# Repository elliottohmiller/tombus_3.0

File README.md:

# tombus_3.0
A barebones noisemaker with a focus on intuitive controls.

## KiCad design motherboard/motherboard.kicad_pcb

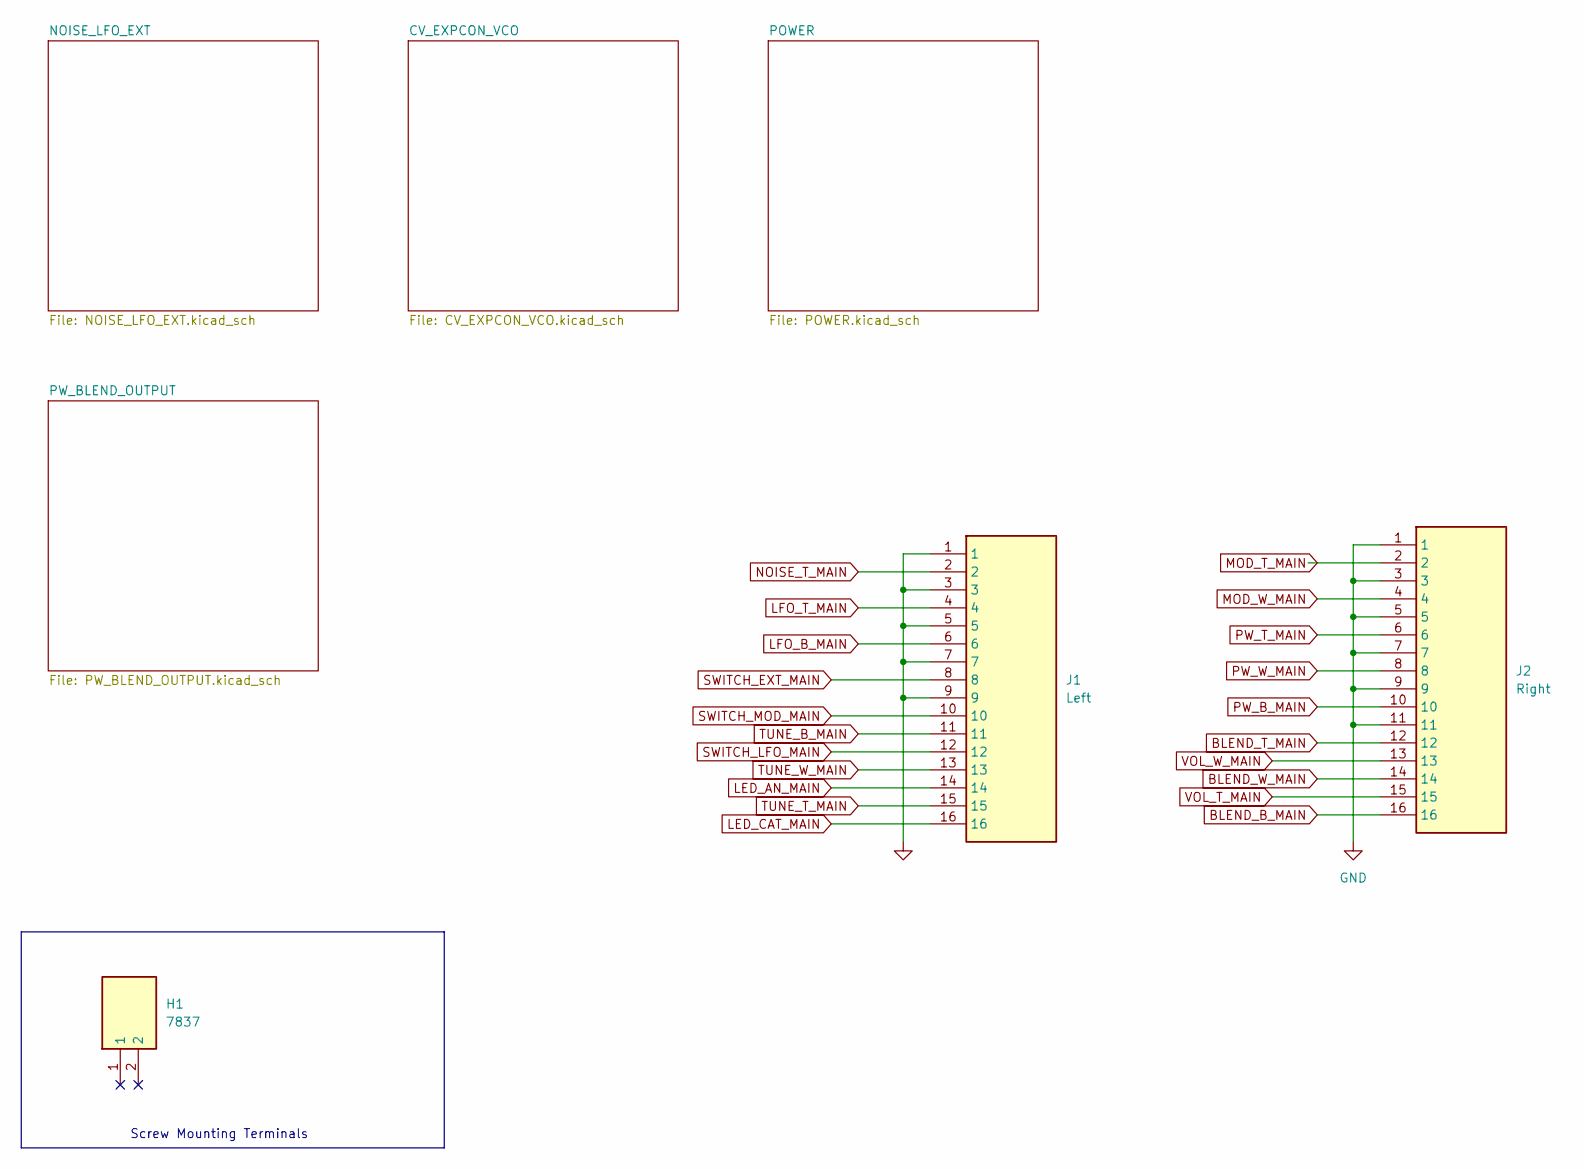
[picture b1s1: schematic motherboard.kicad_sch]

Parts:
H1: 7837; Mouser Part Number 534-7837
J1: Left; HLW16R2C7LF; Mouser Part Number 649-HLW16R-2C7LF
J2: Right; HLW16R2C7LF; Mouser Part Number 649-HLW16R-2C7LF

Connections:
BLEND_B_MAIN: J2.16; also elsewhere on the board
BLEND_T_MAIN: J2.12; also elsewhere on the board
BLEND_W_MAIN: J2.14; also elsewhere on the board
GND: J1.1, J1.3, J1.5, J1.7, J1.9, J2.1, J2.3, J2.5, J2.7, J2.9, J2.11; also elsewhere on the board
LED_AN_MAIN: J1.14; also elsewhere on the board
LED_CAT_MAIN: J1.16; also elsewhere on the board
LFO_B_MAIN: J1.6; also elsewhere on the board
LFO_T_MAIN: J1.4; also elsewhere on the board
MOD_T_MAIN: J2.2; also elsewhere on the board
MOD_W_MAIN: J2.4; also elsewhere on the board
NOISE_T_MAIN: J1.2; also elsewhere on the board
PW_B_MAIN: J2.10; also elsewhere on the board
PW_T_MAIN: J2.6; also elsewhere on the board
PW_W_MAIN: J2.8; also elsewhere on the board
SWITCH_EXT_MAIN: J1.8; also elsewhere on the board
SWITCH_LFO_MAIN: J1.12; also elsewhere on the board
SWITCH_MOD_MAIN: J1.10; also elsewhere on the board
TUNE_B_MAIN: J1.11; also elsewhere on the board
TUNE_T_MAIN: J1.15; also elsewhere on the board
TUNE_W_MAIN: J1.13; also elsewhere on the board
VOL_T_MAIN: J2.15; also elsewhere on the board
VOL_W_MAIN: J2.13; also elsewhere on the board

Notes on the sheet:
Screw Mounting Terminals

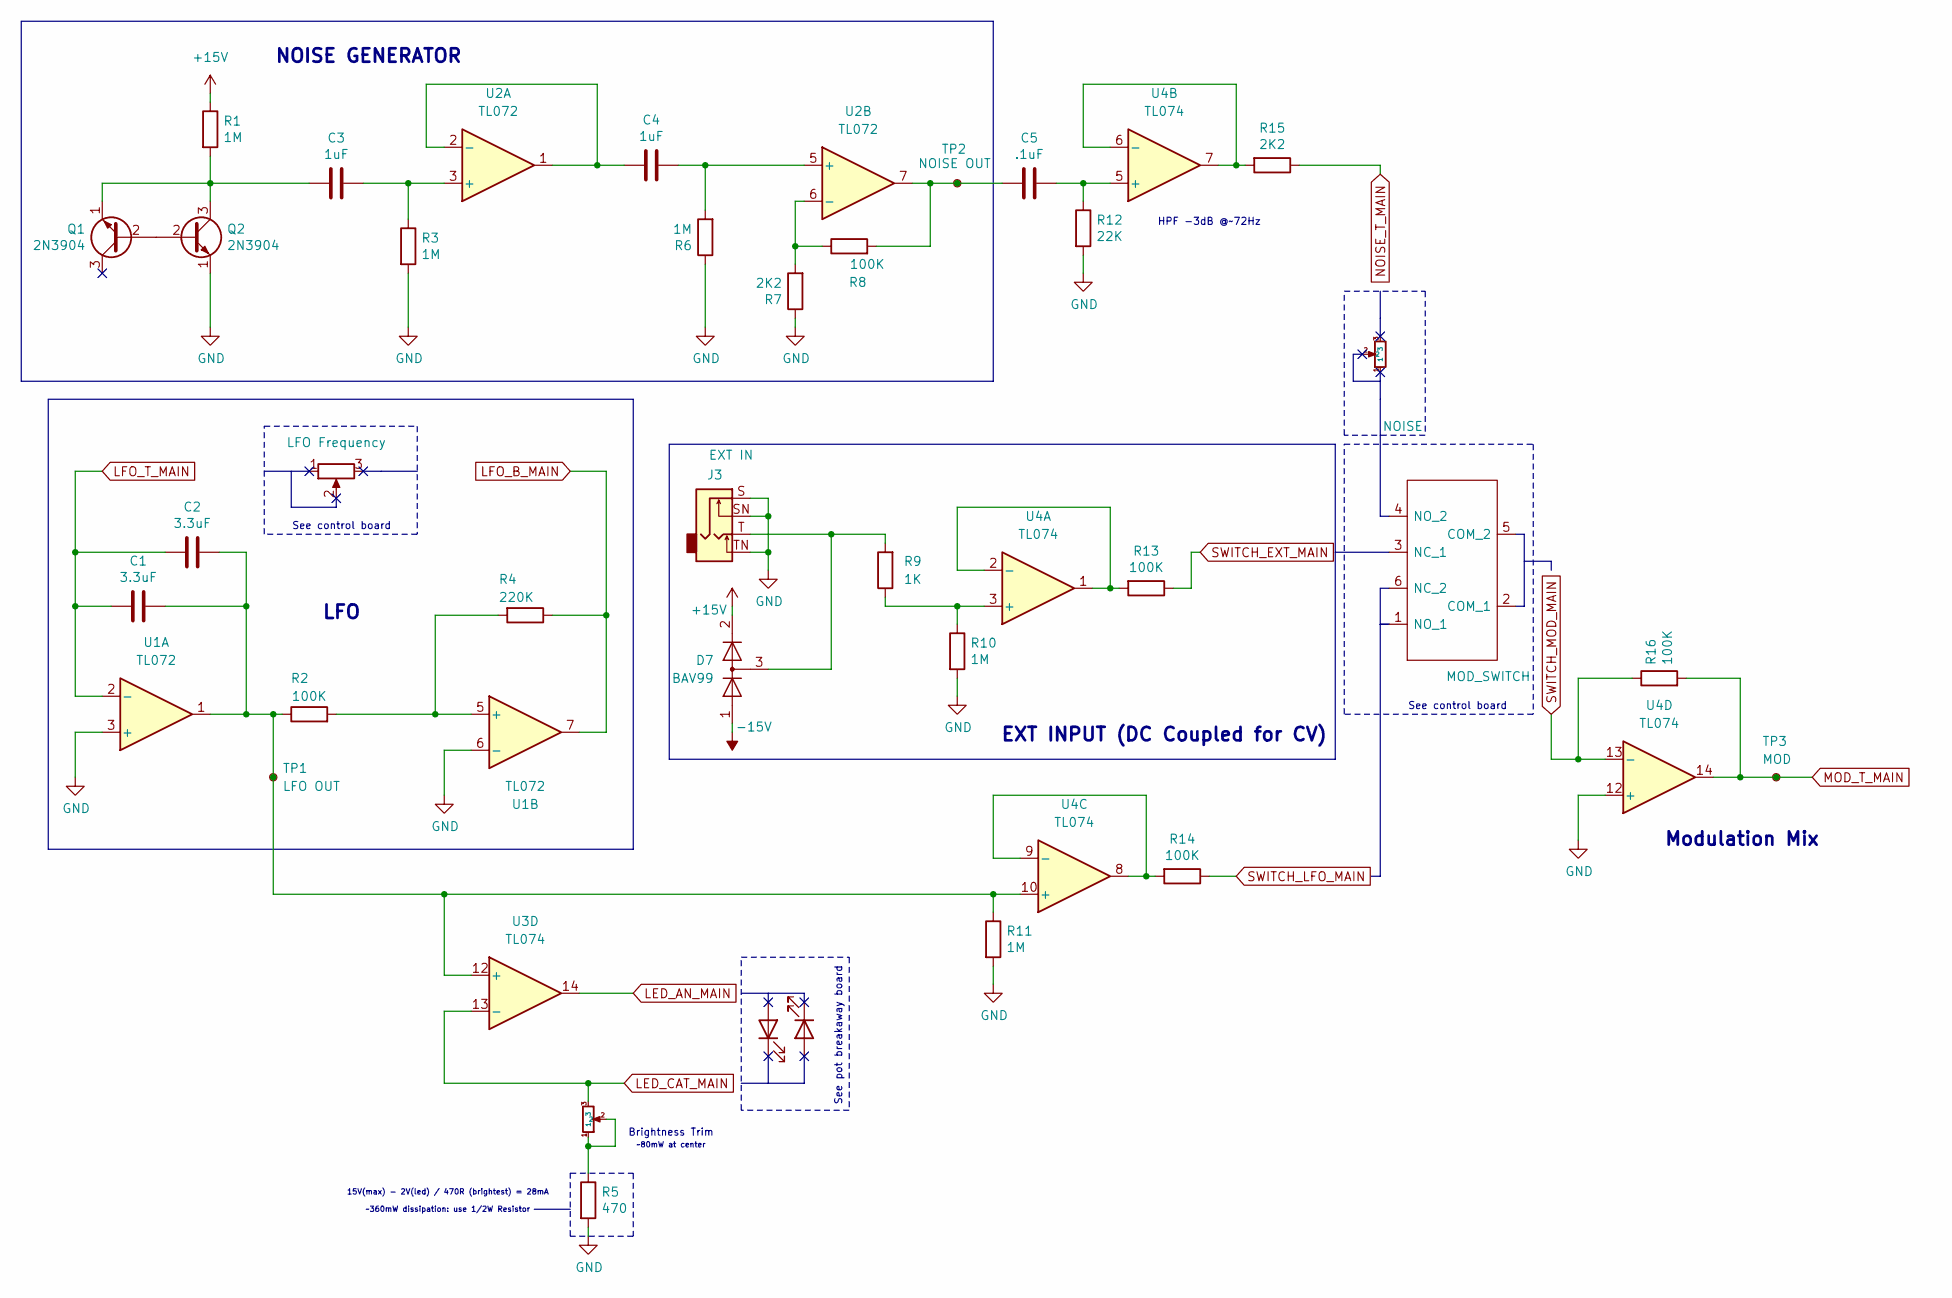
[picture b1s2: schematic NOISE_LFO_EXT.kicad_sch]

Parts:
C1, C2: 3.3uF; C_Rect_L18.0mm_W7.0mm_P15.00mm_FKS3_FKP3
C3, C4: 1uF; C_Rect_L7.2mm_W4.5mm_P5.00mm_FKS2_FKP2_MKS2_MKP2
C5: .1uF; C_Rect_L7.0mm_W2.0mm_P5.00mm
D1, D2: LFO F
D7: BAV99; SOT-23
J3: EXT IN; Jack_6.35mm_Neutrik_NMJ4HFD2_Horizontal
Q1, Q2: 2N3904; TO-92_HandSolder
R1, R3, R6, R10, R11: 1M; RESC2012X60N
R2, R8, R13, R14, R16: 100K; RESC2012X60N
R4: 220K; RESC2012X60N
R5: 470; R_Axial_DIN0207_L6.3mm_D2.5mm_P10.16mm_Horizontal
R7, R15: 2K2; RESC2012X60N
R9: 1K; RESC2012X60N
R12: 22K; RESC2012X60N
RV1: LFO Frequency
S1: MOD_SWITCH; 7211SYCQE; Mouser Part Number 611-7211-002
TP1: LFO OUT; TestPoint_Pad_D1.5mm
TP2: NOISE OUT; TestPoint_Pad_D1.5mm
TP3: MOD; TestPoint_Pad_D1.5mm
U1, U2: TL072; DIP-8_W7.62mm_Socket
U3, U4: TL074; DIP-14_W7.62mm_Socket
VR1: LED BRIGHTNESS; Potentiometer_Vishay_T73XX_Horizontal; Mouser Part Number 72-T70YP-10K
VR2: NOISE; T73YP103KT20; Mouser Part Number 72-T70YP-10K

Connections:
+15V: D7.2 (A), R1.1; also elsewhere on the board
-15V: D7.1 (K); also elsewhere on the board
GND: J3.S, J3.SN, J3.TN, Q2.1 (E), R3.2, R5.2, R6.1, R7.1, R10.2, R11.2, R12.2, U1.3 (+), U1.6 (-), U4.12 (+); also elsewhere on the board
LED_AN_MAIN: U3.14; also elsewhere on the board
LED_CAT_MAIN: U3.13 (-), VR1.3; also elsewhere on the board
LFO_B_MAIN: R4.1, U1.7; also elsewhere on the board
LFO_T_MAIN: C1.2, C2.2, U1.2 (-); also elsewhere on the board
MOD_T_MAIN: R16.2, TP3.1, U4.14; also elsewhere on the board
NOISE_T_MAIN: R15.1; also elsewhere on the board
unnamed: C5.2, R8.2, TP2.1, U2.7
unnamed: D7.3 (K), J3.T, R9.2
unnamed: Q1.2 (B), Q2.2 (B)
unnamed: C3.2, Q1.1 (E), Q2.3 (C), R1.2
unnamed: R5.1, VR1.1, VR1.2
unnamed: R2.2, R4.2, U1.5 (+)
unnamed: C3.1, R3.1, U2.3 (+)
unnamed: C4.2, U2.1, U2.2 (-)
unnamed: C4.1, R6.2, U2.5 (+)
unnamed: R7.2, R8.1, U2.6 (-)
unnamed: C1.1, C2.1, R2.1, R11.1, TP1.1, U1.1, U3.12 (+), U4.10 (+)
unnamed: R9.1, R10.1, U4.3 (+)
unnamed: R13.2, U4.1, U4.2 (-)
unnamed: C5.1, R12.1, U4.5 (+)
unnamed: R15.2, U4.6 (-), U4.7
unnamed: R14.2, U4.8, U4.9 (-)
SWITCH_EXT_MAIN: R13.1; also elsewhere on the board
SWITCH_LFO_MAIN: R14.1; also elsewhere on the board
SWITCH_MOD_MAIN: R16.1, U4.13 (-); also elsewhere on the board

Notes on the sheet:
Brightness Trim
NOISE GENERATOR
LFO
15V(max) - 2V(led) / 470R (brightest) = 28mA ~360mW dissipation: use 1/2W Resistor
See control board
See pot breakaway board
~80mW at center
HPF -3dB @~72Hz
EXT INPUT (DC Coupled for CV)
Modulation Mix

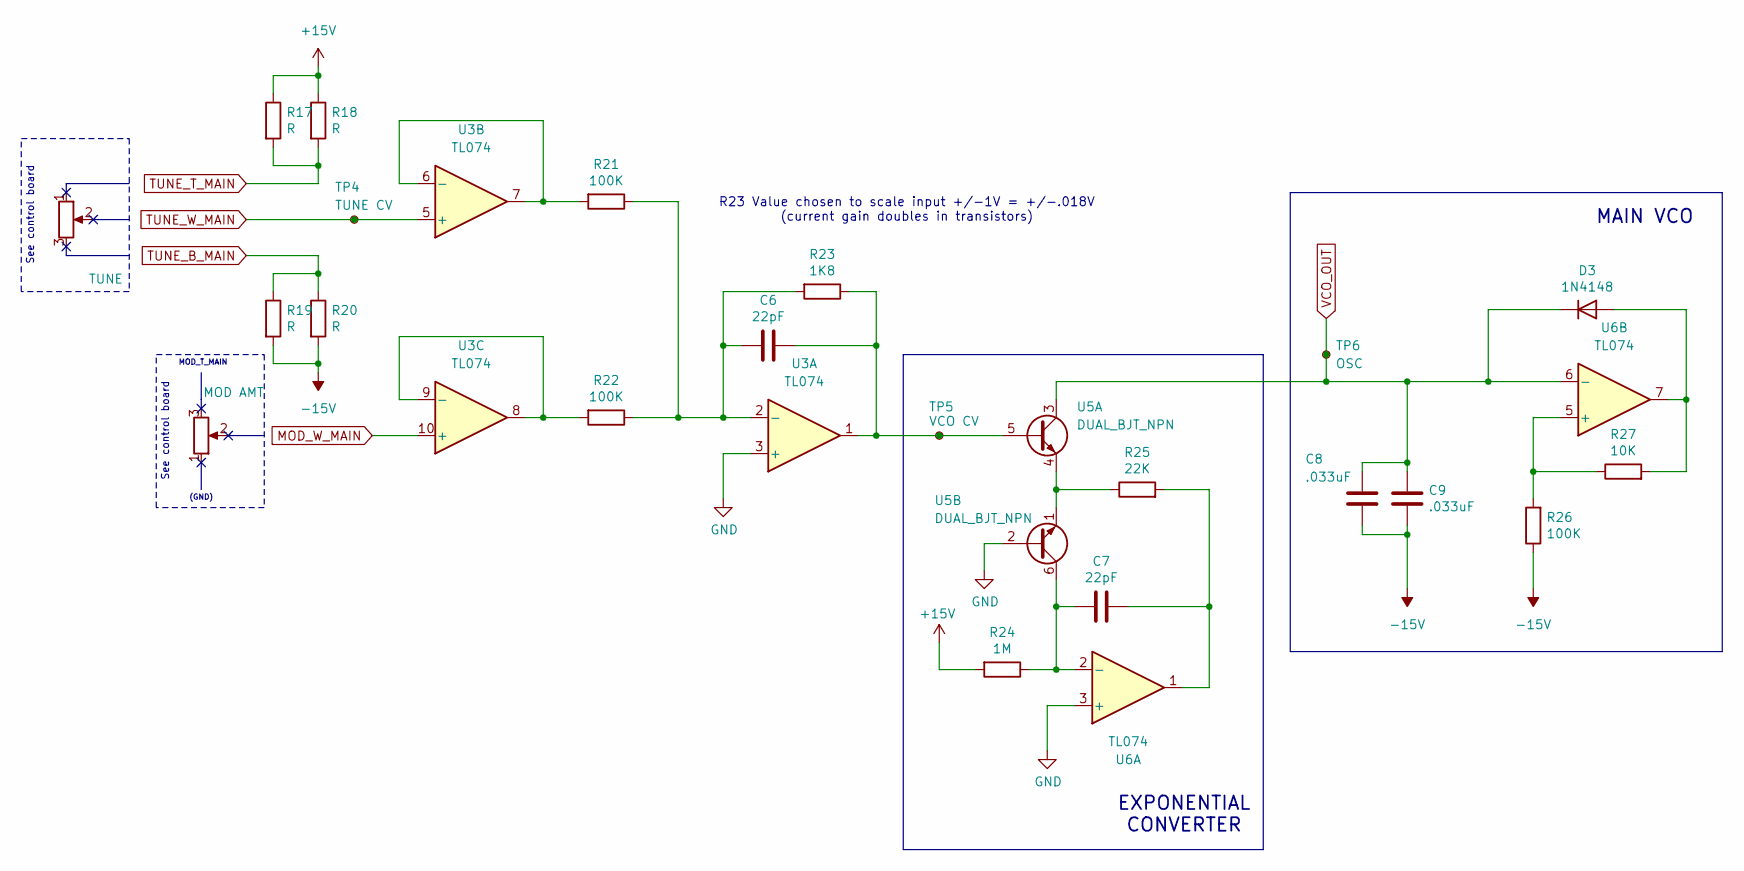
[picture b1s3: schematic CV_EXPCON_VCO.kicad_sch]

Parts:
C6, C7: 22pF; C0805
C8, C9: .033uF; C_Rect_L7.2mm_W8.5mm_P5.00mm_FKP2_FKP2_MKS2_MKP2
D3: 1N4148; D_DO-35_SOD27_P7.62mm_Horizontal
R17, R18, R19, R20: R; RESC2012X60N
R21, R22, R26: 100K; RESC2012X60N
R23: 1K8; RESC2012X60N
R24: 1M; RESC2012X60N
R25: 22K; RESC2012X60N
R27: 10K; RESC2012X60N
RV2: TUNE
RV3: MOD AMT
TP4: TUNE CV; TestPoint_Pad_D1.5mm
TP5: VCO CV; TestPoint_Pad_D1.5mm
TP6: OSC; TestPoint_Pad_D1.5mm
U3, U6: TL074; DIP-14_W7.62mm_Socket
U5: DUAL_BJT_NPN; SOT-363_SC-70-6

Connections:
+15V: R17.1, R18.1, R24.2; also elsewhere on the board
-15V: C8.1, C9.1, R19.2, R20.2, R26.1; also elsewhere on the board
GND: U3.3 (+), U5.2 (B1), U6.3 (+); also elsewhere on the board
MOD_W_MAIN: U3.10 (+); also elsewhere on the board
unnamed: C7.1, R25.2, U6.1
unnamed: D3.2 (A), R27.2, U6.7
unnamed: C6.2, R21.1, R22.1, R23.2, U3.2 (-)
unnamed: R21.2, U3.6 (-), U3.7
unnamed: R22.2, U3.8, U3.9 (-)
unnamed: C6.1, R23.1, TP5.1, U3.1, U5.5 (B2)
unnamed: R25.1, U5.1 (E2), U5.4 (E1)
unnamed: C7.2, R24.1, U5.6 (C2), U6.2 (-)
unnamed: R26.2, R27.1, U6.5 (+)
TUNE_B_MAIN: R19.1, R20.1; also elsewhere on the board
TUNE_T_MAIN: R17.2, R18.2; also elsewhere on the board
TUNE_W_MAIN: TP4.1, U3.5 (+); also elsewhere on the board
VCO_OUT: C8.2, C9.2, D3.1 (K), TP6.1, U5.3 (C1), U6.6 (-); also elsewhere on the board

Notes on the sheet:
See control board
MOD_T_MAIN
R23 Value chosen to scale input +/-1V = +/-.018V (current gain doubles in transistors)
MAIN VCO
EXPONENTIAL CONVERTER
(GND)

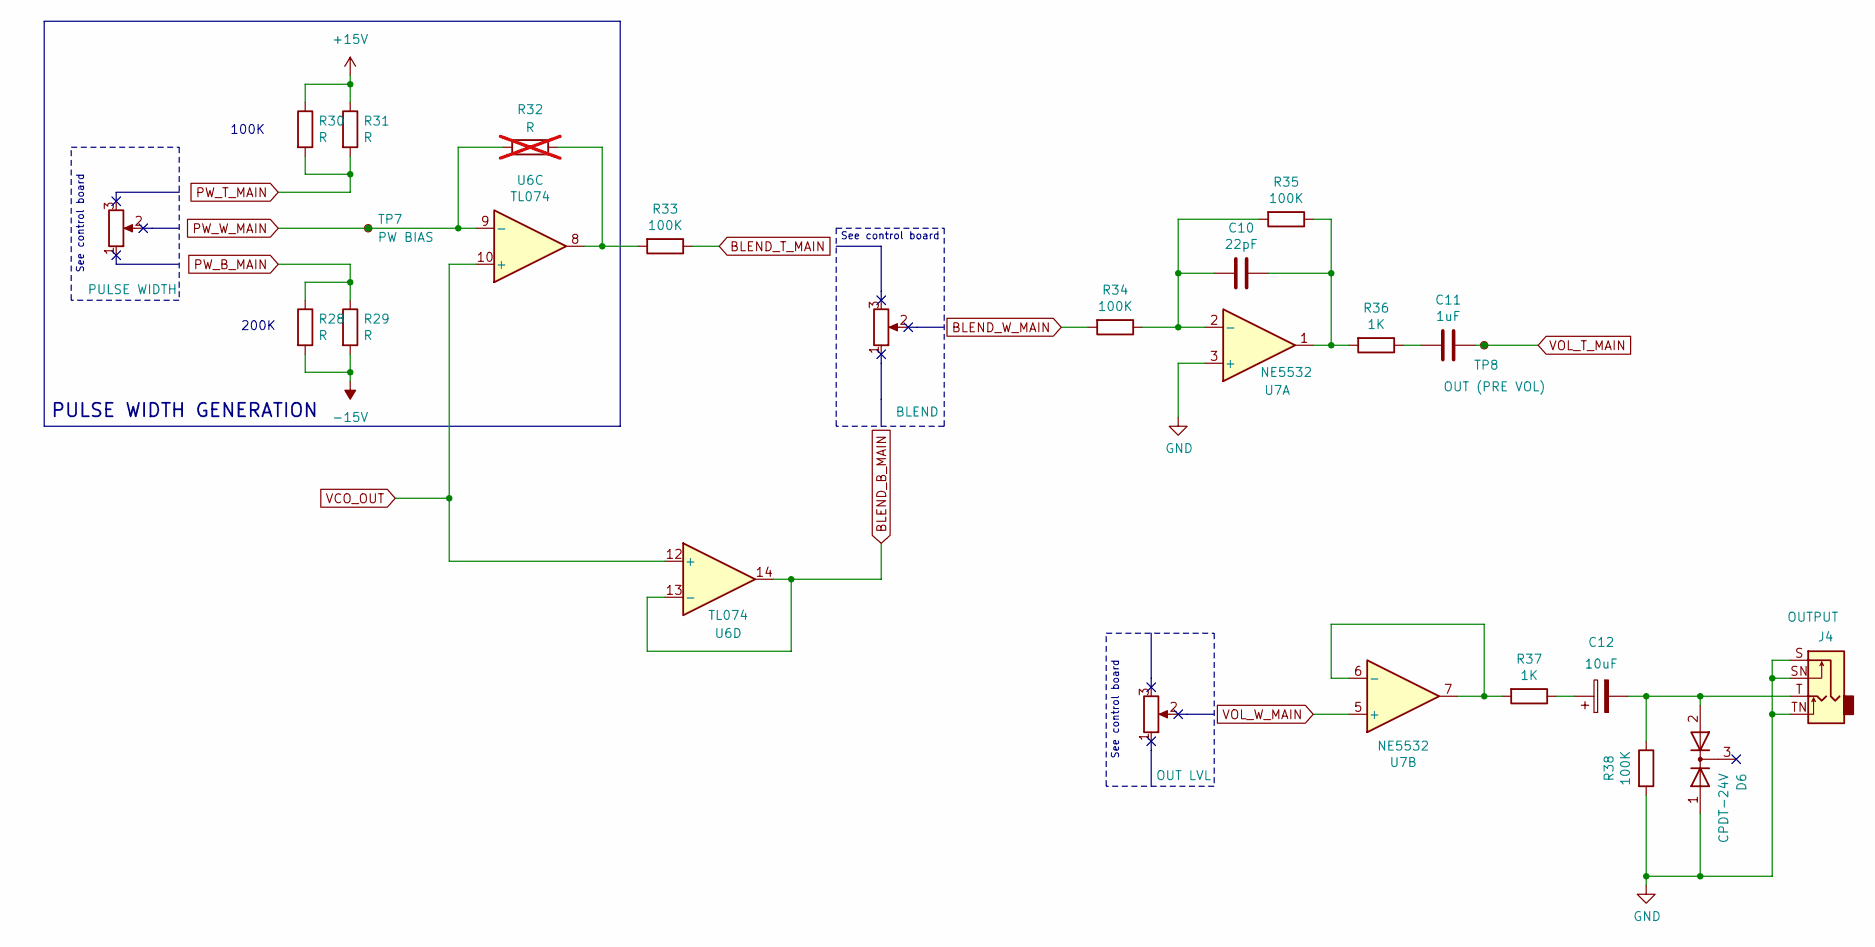
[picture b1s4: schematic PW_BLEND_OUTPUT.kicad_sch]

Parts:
C10: 22pF; C0805
C11: 1uF; C_Rect_L7.2mm_W4.5mm_P5.00mm_FKS2_FKP2_MKS2_MKP2
C12: 10uF; CP_Radial_D5.0mm_P2.00mm
D6: CPDT-24V; SOT-23
J4: OUTPUT; Jack_6.35mm_Neutrik_NMJ4HFD2_Horizontal
R28, R29, R30, R31: R; RESC2012X60N
R32: R; RESC2012X60N; not fitted
R33, R34, R35, R38: 100K; RESC2012X60N
R36, R37: 1K; RESC2012X60N
RV4: PULSE WIDTH
RV5: BLEND
RV6: OUT LVL
TP7: PW BIAS; TestPoint_Pad_D1.5mm
TP8: OUT (PRE VOL); TestPoint_Pad_D1.5mm
U6: TL074; DIP-14_W7.62mm_Socket
U7: NE5532; DIP-8_W7.62mm_Socket

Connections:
+15V: R30.1, R31.1; also elsewhere on the board
-15V: R28.2, R29.2; also elsewhere on the board
BLEND_B_MAIN: U6.13 (-), U6.14; also elsewhere on the board
BLEND_T_MAIN: R33.1; also elsewhere on the board
BLEND_W_MAIN: R34.2; also elsewhere on the board
GND: D6.1 (A), J4.S, J4.SN, J4.TN, R38.2, U7.3 (+); also elsewhere on the board
unnamed: C10.1, R35.1, R36.2, U7.1
unnamed: C11.2, R36.1
unnamed: C12.1, R37.1
unnamed: C12.2, D6.2 (A), J4.T, R38.1
unnamed: R32.2, R33.2, U6.8
unnamed: C10.2, R34.1, R35.2, U7.2 (-)
unnamed: R37.2, U7.6 (-), U7.7
PW_B_MAIN: R28.1, R29.1; also elsewhere on the board
PW_T_MAIN: R30.2, R31.2; also elsewhere on the board
PW_W_MAIN: R32.1, TP7.1, U6.9 (-); also elsewhere on the board
VCO_OUT: U6.10 (+), U6.12 (+); also elsewhere on the board
VOL_T_MAIN: C11.1, TP8.1; also elsewhere on the board
VOL_W_MAIN: U7.5 (+); also elsewhere on the board

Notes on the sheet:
See control board
200K
100K
PULSE WIDTH GENERATION

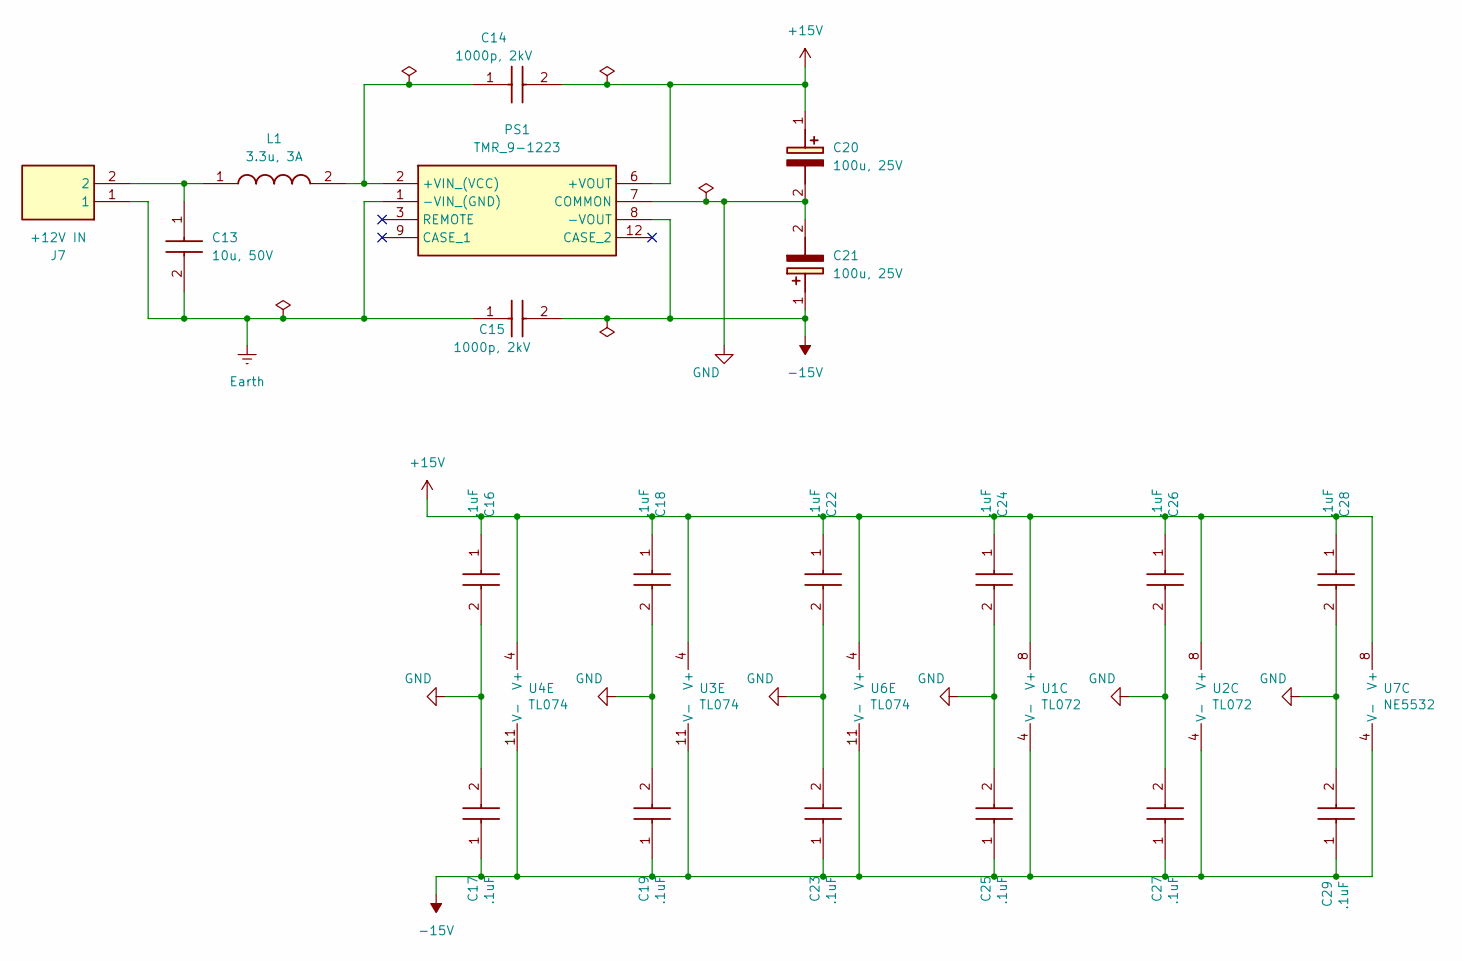
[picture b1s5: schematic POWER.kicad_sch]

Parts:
C13: 10u, 50V; C1210; Mouser Part Number 80-C1210C106M5R
C14, C15: 1000p, 2kV; C1206; Mouser Part Number 80-C1206C102JGR
C16, C17, C18, C19, C22, C23, C24, C25, C26, C27, C28, C29: .1uF; C0805; Mouser Part Number 80-C0805C104K1R
C20, C21: 100u, 25V; CAPPRD250W55D630H1350; Mouser Part Number 581-RES0611101M025B
J7: +12V IN; SHDR2W66P0X254_1X2_508X572X1041P; Mouser Part Number 571-6404562
L1: 3.3u, 3A; INDPM4740X210N; Mouser Part Number 495-TCK-108
PS1: TMR_9-1223; TMR92411; Mouser Part Number 495-TMR9-1223
U1, U2: TL072; DIP-8_W7.62mm_Socket
U3, U4, U6: TL074; DIP-14_W7.62mm_Socket
U7: NE5532; DIP-8_W7.62mm_Socket

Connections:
+15V: C14.2, C16.1, C18.1, C20.1 (+), C22.1, C24.1, C26.1, C28.1, PS1.6 (+VOUT), U1.8 (V+), U2.8 (V+), U3.4 (V+), U4.4 (V+), U6.4 (V+), U7.8 (V+); also elsewhere on the board
-15V: C15.2, C17.1, C19.1, C21.1 (+), C23.1, C25.1, C27.1, C29.1, PS1.8 (-VOUT), U1.4 (V-), U2.4 (V-), U3.11 (V-), U4.11 (V-), U6.11 (V-), U7.4 (V-); also elsewhere on the board
Earth: C13.2, C15.1, J7.1, PS1.1 (-VIN_(GND))
GND: C16.2, C17.2, C18.2, C19.2, C20.2 (-), C21.2 (-), C22.2, C23.2, C24.2, C25.2, C26.2, C27.2, C28.2, C29.2, PS1.7 (COMMON); also elsewhere on the board
unnamed: C13.1, J7.2, L1.1
unnamed: C14.1, L1.2, PS1.2 (+VIN_(VCC))

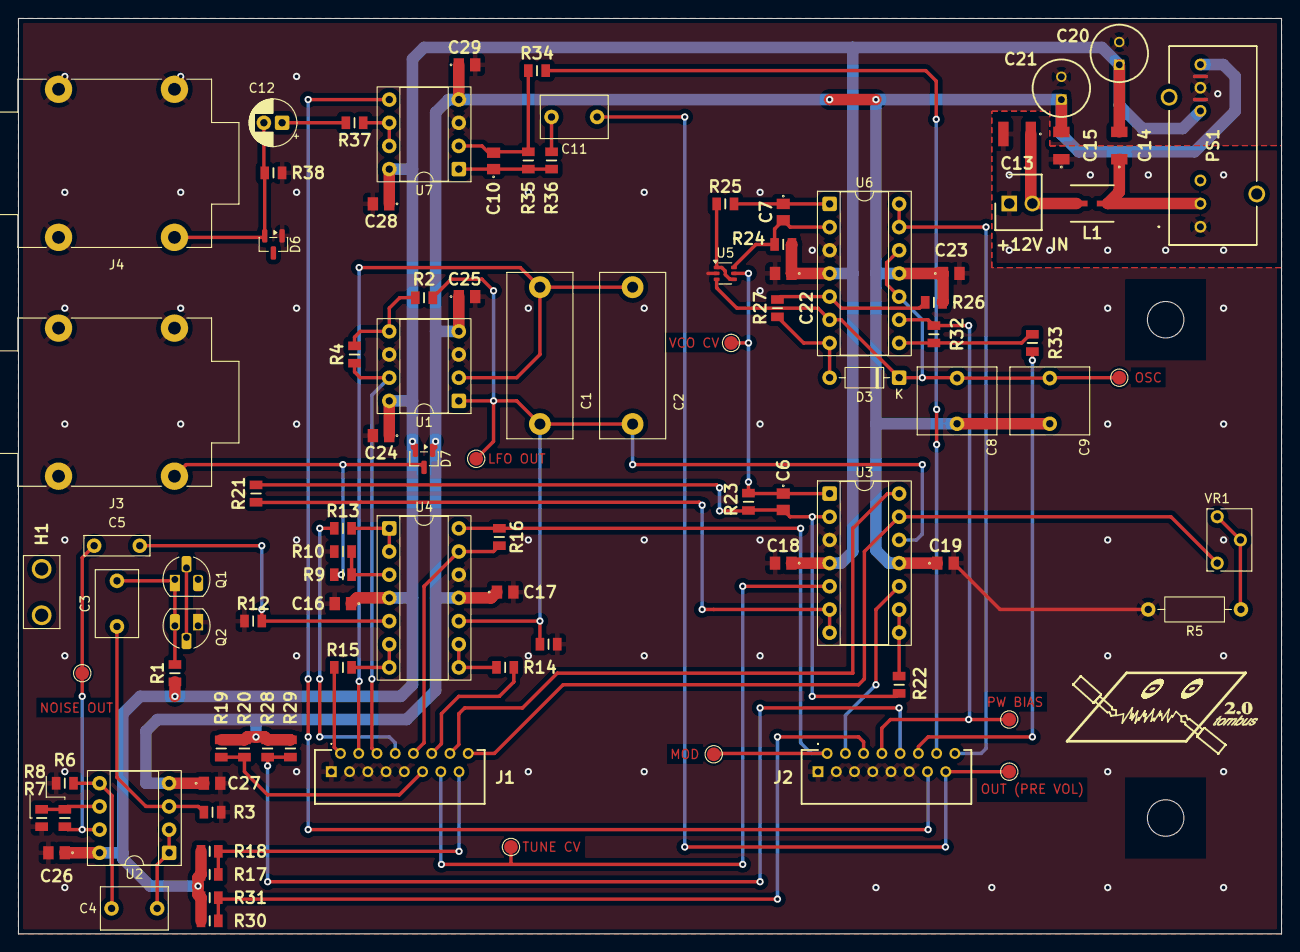
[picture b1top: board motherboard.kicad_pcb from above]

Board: 2 copper layers, 138.4 x 100.3 mm, 96 parts (0 on the bottom side), 60 nets.

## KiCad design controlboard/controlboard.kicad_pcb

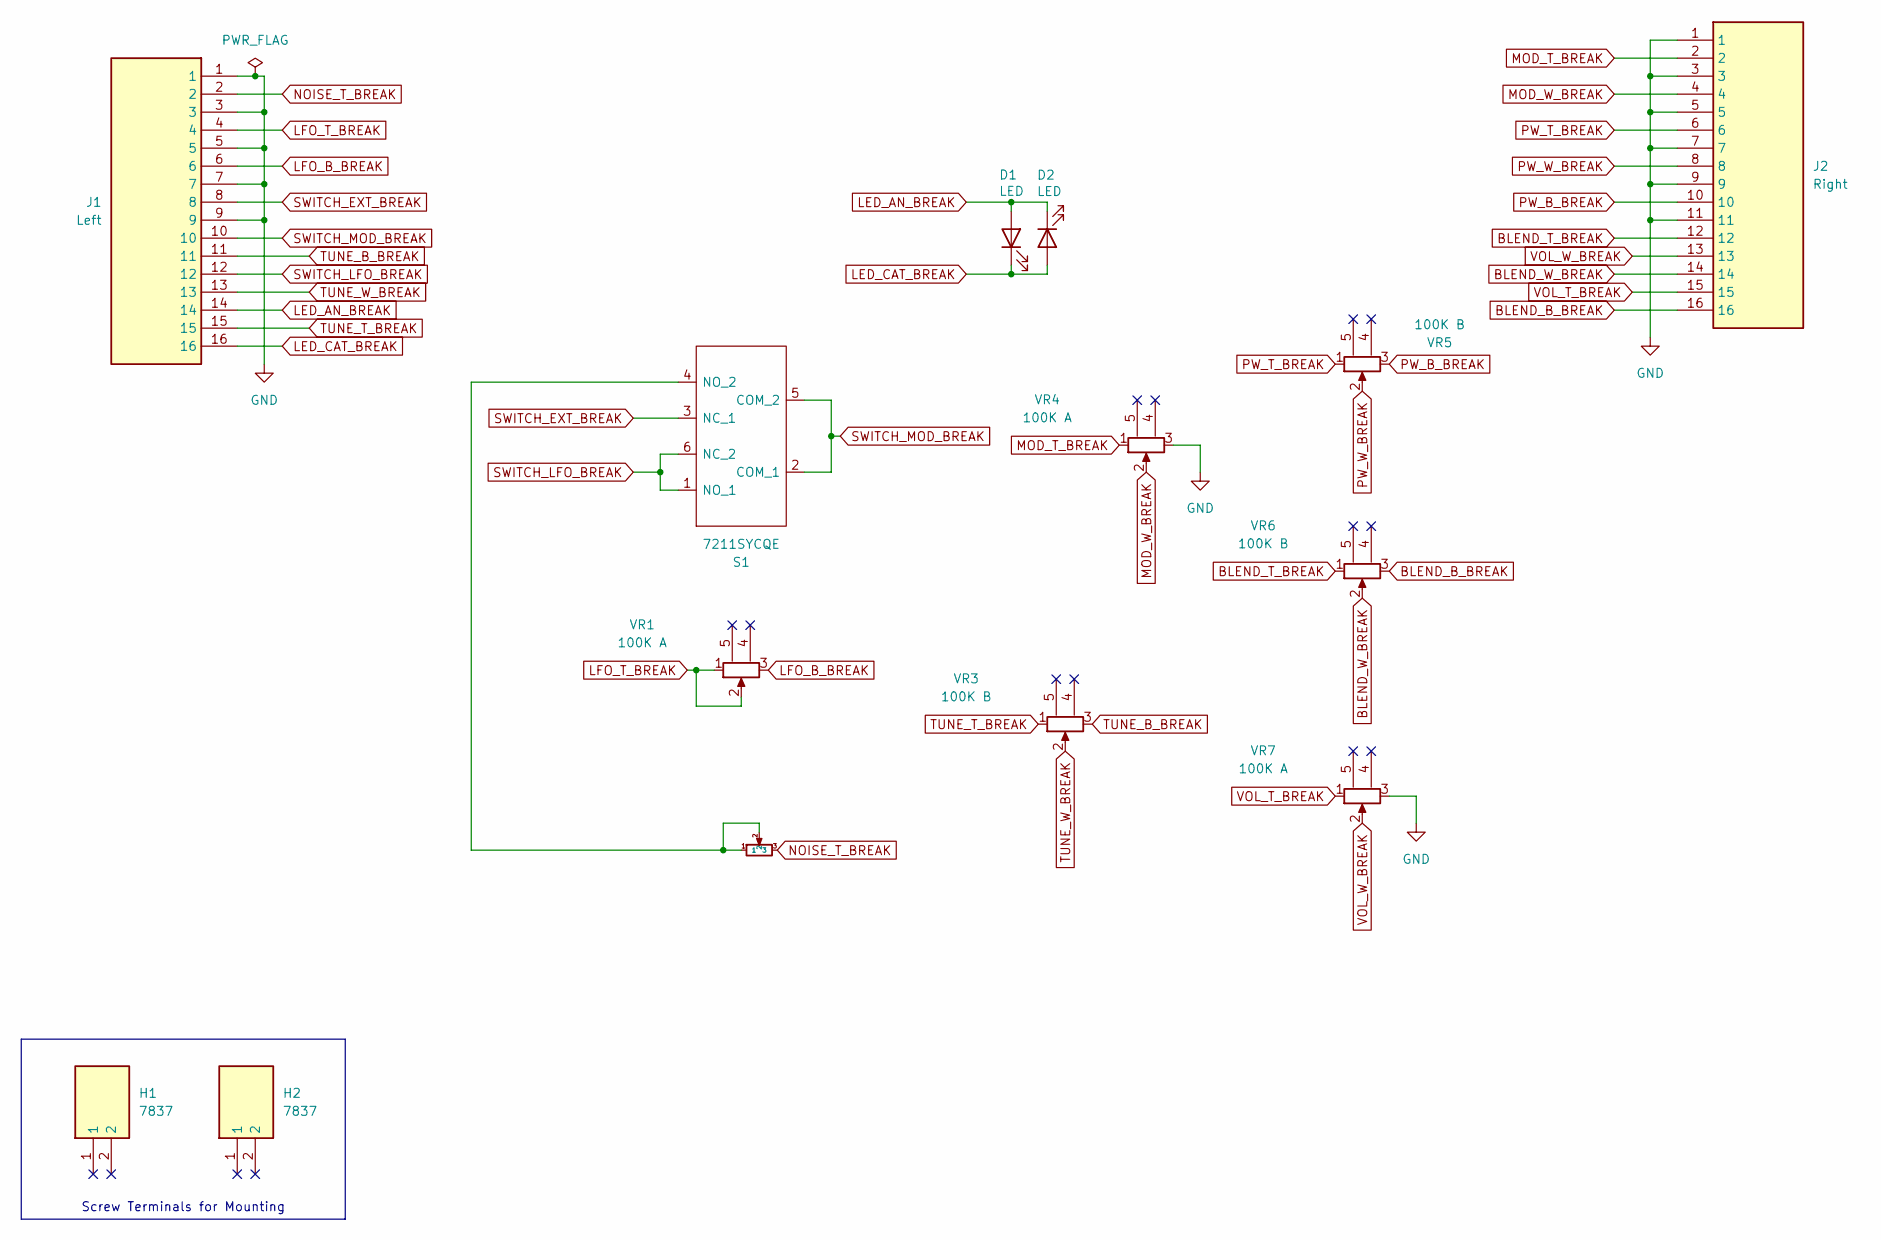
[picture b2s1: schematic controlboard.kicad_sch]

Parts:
D1, D2: LED; LED_D3.0mm_Clear
H1, H2: 7837; Mouser Part Number 534-7837
J1: Left; HLW16R2C7LF; Mouser Part Number 649-HLW16R-2C7LF
J2: Right; HLW16R2C7LF; Mouser Part Number 649-HLW16R-2C7LF
S1: 7211SYCQE; Mouser Part Number 611-7211-002
VR1, VR4, VR7: 100K A; PTN091V100115K1A; Manufacturer_Part_Number PTN091-V100115K1A
VR2: T73YP103KT20; Mouser Part Number 72-T70YP-10K
VR3, VR5, VR6: 100K B; PTN091V100115K1B; Manufacturer_Part_Number PTN091-V100115K1B

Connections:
BLEND_B_BREAK: J2.16, VR6.3
BLEND_T_BREAK: J2.12, VR6.1
BLEND_W_BREAK: J2.14, VR6.2
GND: J1.1, J1.3, J1.5, J1.7, J1.9, J2.1, J2.3, J2.5, J2.7, J2.9, J2.11, VR4.3, VR7.3
LED_AN_BREAK: D1.2 (A), D2.1 (K), J1.14
LED_CAT_BREAK: D1.1 (K), D2.2 (A), J1.16
LFO_B_BREAK: J1.6, VR1.3
LFO_T_BREAK: J1.4, VR1.1, VR1.2
MOD_T_BREAK: J2.2, VR4.1
MOD_W_BREAK: J2.4, VR4.2
NOISE_T_BREAK: J1.2, VR2.3
unnamed: S1.4 (NO_2), VR2.1, VR2.2
PW_B_BREAK: J2.10, VR5.3
PW_T_BREAK: J2.6, VR5.1
PW_W_BREAK: J2.8, VR5.2
SWITCH_EXT_BREAK: J1.8, S1.3 (NC_1)
SWITCH_LFO_BREAK: J1.12, S1.1 (NO_1), S1.6 (NC_2)
SWITCH_MOD_BREAK: J1.10, S1.2 (COM_1), S1.5 (COM_2)
TUNE_B_BREAK: J1.11, VR3.3
TUNE_T_BREAK: J1.15, VR3.1
TUNE_W_BREAK: J1.13, VR3.2
VOL_T_BREAK: J2.15, VR7.1
VOL_W_BREAK: J2.13, VR7.2

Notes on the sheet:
Screw Terminals for Mounting

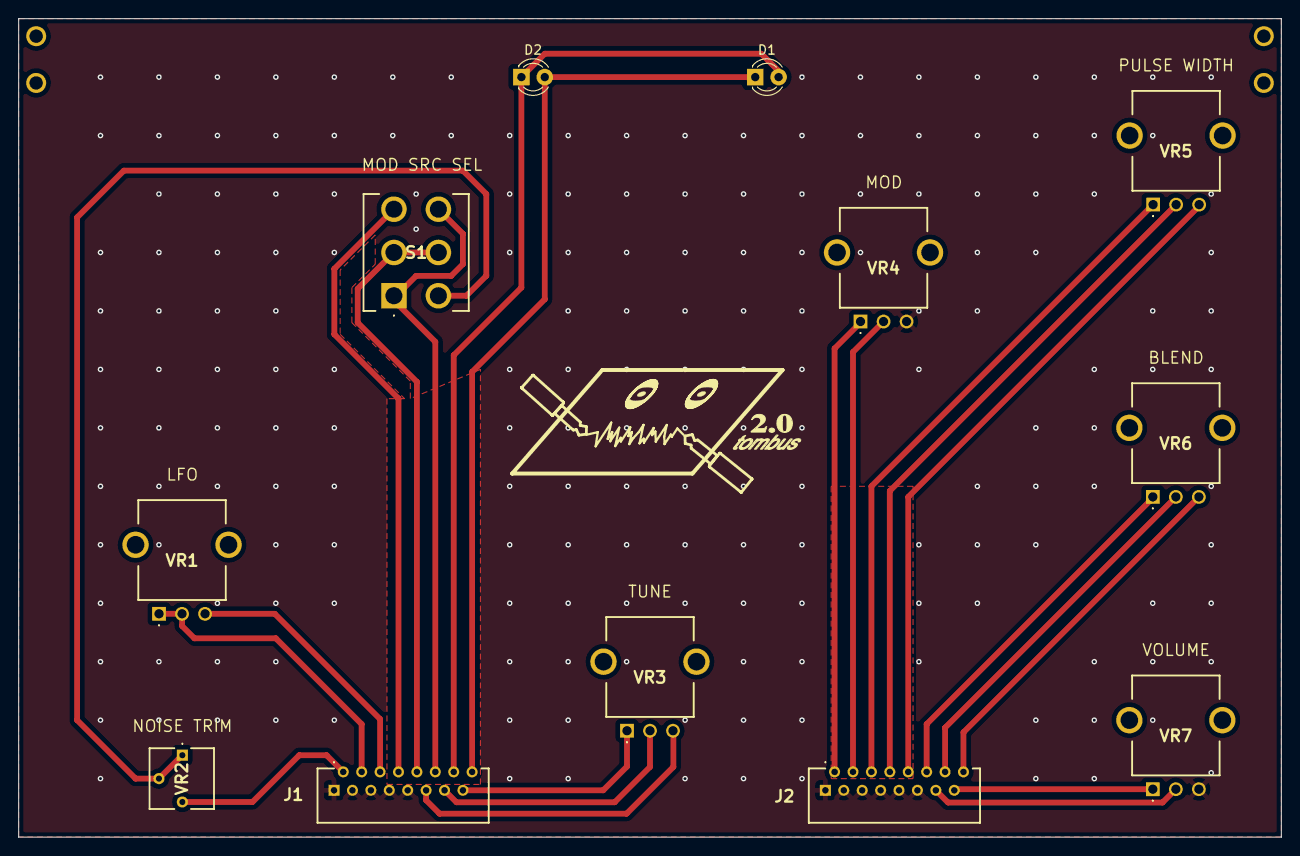
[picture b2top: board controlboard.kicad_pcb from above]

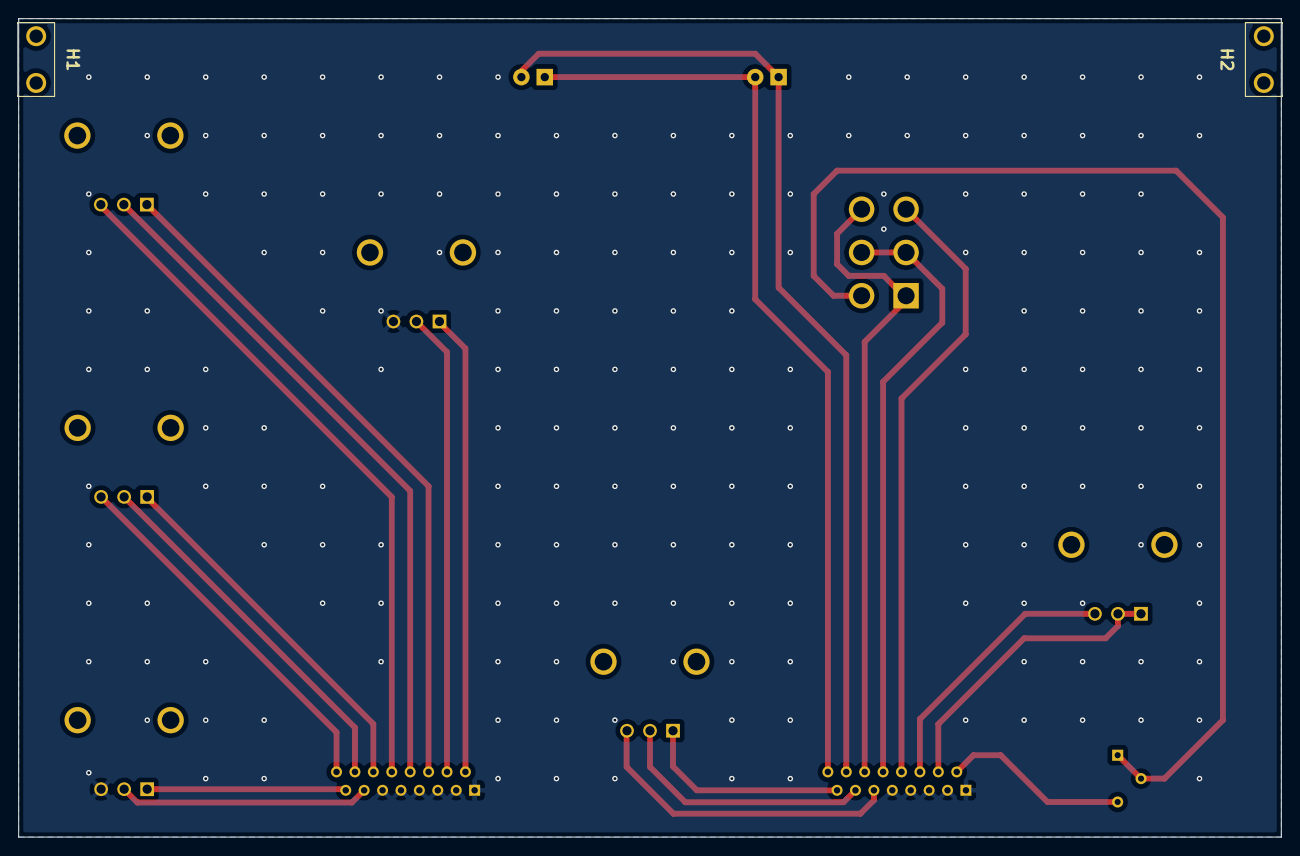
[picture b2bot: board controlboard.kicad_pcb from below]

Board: 2 copper layers, 137.2 x 88.9 mm, 14 parts (2 on the bottom side), 23 nets.

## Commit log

2026-02-08 init
2026-02-08 remove motherboard as submodule
2026-02-08 add model to CAD outputs
2026-02-08 Enhance README with image and description
    Added an image to the README for better visualization.
2026-02-08 add pdfs
